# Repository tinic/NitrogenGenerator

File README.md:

# Nitrogen Generator for Home Brewing

> DIY membrane nitrogen generator for **nitro cold brew coffee**, **nitro stout**, and beverage push-gas service. Extracts **99.5%+ pure N₂** from compressed air. Total build cost **$2,222** — about half the price of commercial alternatives like NitroBev 360 or NitroBrew.

## At a glance

| Spec | Value |
|---|---|
| Output flow | 50 L/h (2 CFH) at 100 PSI |
| Output purity | 99.5%+ nitrogen (≤0.5% O₂) |
| Compressed-air input | ≤ 30 L/h (1 CFM) |
| Operating pressure | 75–100 PSI |
| Air-to-N₂ ratio | ~5:1 |
| Power | 120/240 V AC (idle = 0 W; runs only when refilling) |
| Membrane | KL-AIR MNH-1512A |
| Holding tank | 5 gal Cornelius keg |
| Total cost | **$2,222** |

### Cost vs. commercial alternatives

| Option | Cost |
|---|---|
| **This DIY build** | **$2,222** |
| NitroBev 360 | ~$4,500 |
| Industrial PSA nitrogen generator | $8,000+ |

## Motivation

As a home brewer CO₂ is the gas of choice for most purposes, including pushing beverages to the tap. But sometimes you don't want to just serve beer but also cold brew coffee and other non-carbonated beverages. In most cases a simple N₂ cylinder does the job — but given that air is 78% nitrogen, why not just extract it from the air? Recently products like NitroBev 360 have introduced this possibility on a small scale, at a price. Given the huge margins these niche products have to have, my thought was to build a nitrogen generator from scratch for less.

**Use cases this build is sized for:**

- Nitro cold brew coffee on draft
- Nitro stout / Guinness-style cascading head
- Wine and whiskey blanketing during long pours
- Generic beverage push gas where CO₂ would over-carbonate

## How nitrogen generators work

This project uses **membrane separation**. A membrane-based nitrogen generator works by passing compressed air through a semi-permeable membrane made of bundles of hollow polymer fibers. Oxygen and water vapor molecules, being smaller and having a higher permeation rate, pass through the membrane walls and are vented out as permeate. Nitrogen molecules, being larger and slower to permeate, remain inside the fibers and exit at the outlet as a high-purity nitrogen stream. Purity is adjustable down to about 0.5% residual oxygen — well within spec for beverage service.

A membrane generator needs **continuous compressed-air flow** to work. The separation relies on a sustained pressure differential across the fiber walls; if the air supply is intermittent or undersized, the differential collapses and oxygen leaks straight through. The membrane is also engineered for a specific air-flow band — undershoot it and the gas dynamics break down well before you're starving on volume.

A small **needle valve on the membrane output** controls purity. Open it too far and the residence time inside the fiber drops, producing high-O₂ output. Close it too far and most of your compressed air is dumped overboard as permeate, killing efficiency. This adjustment is per-membrane and is the single most important calibration step in the build.

The membrane needs **clean air**. Compressed air carries dust, oil aerosols, water vapor, and hydrocarbons; any of those will foul the polymer fibers. Without proper filtration, a membrane that should last *years* will die in *hours*. We filter down to **0.01 µm** before the air sees the membrane.

### Membrane vs. PSA — why membrane

PSA (Pressure Swing Adsorption) generators reach higher purity (down to a few ppm O₂) but use molecular-sieve beds, twin-tower switching valves, and large compressors — overkill for home use, expensive, and noisy. Membrane is the right scale here: no moving parts, low power, scales down to 50 L/h cleanly, and 99.5% purity is more than enough for beverage service.

## Goals & target metrics

Most commercial large-scale nitrogen equipment is built for continuous N₂ blanketing. We don't need that — a home brewer fills a keg now and then. The design priorities:

- Optimize for **low power** and **casual use**
- **Idle = zero power** (the system only runs when nitrogen is being made)
- Use **readily available, serviceable** components
- **Reasonable N₂ output** for the application — one keg per hour is plenty
- **Portable** — fits in a stainless enclosure, plugs into 120 V
- Reuse equipment home brewers already have (Cornelius keg as accumulator)

Resulting numbers:

- **120/240 V household power** — works on a generator too
- **~50 L/h (2 CFH)** N₂ output — about one keg per hour
- **≤30 L/h (1 CFM)** compressed-air input — small quiet portable compressor is fine
- **100 PSI max** system pressure — Cornelius keg territory

## Skills required

- Hands-on experience with pressurized vessels (kegging-pressure literacy is enough)
- Programming a PLC, Arduino, or microcontroller — the controller is custom firmware here, but ladder logic is fine too
- Comfort with NPT and 8 mm push-in pneumatic fittings, basic leak chasing
- Reading a P&ID
- Multimeter and soldering iron at the level of "I've put together a kit before"

## Bill of materials

These are the actual parts I bought, with what I paid. Substitutes are fine where noted; the membrane and the air filter are the two parts you should not cheap out on.

| # | Component | Model / part | Source | Paid | Notes |
|---|---|---|---|---|---|
| 1 | Nitrogen membrane | [MNH-1512A](./docs/MNH-1512A.pdf) | KL-AIR (Alibaba) | $400 | 50 L/h @ 100 PSI, 99.5%; 120 PSI max input |
| 2 | 3-stage air filter | PneumaticPlus SAFU460-N04-MEP | Amazon | $200 | 0.01 µm coalescing final stage — **don't skimp** |
| 3 | Air compressor | Makita MAC100Q | Hardware store | $250 | Quiet, ~1 CFM, oil-free |
| 4 | O₂ analyzer | FORENSICS O₂ Analyzer | Amazon | $200 | 0–30%, must support flow-through (tube fitting) |
| 5 | Holding tank | 5 gal Cornelius keg | Homebrew supplier | $130 | |
| 6 | Controller | Custom STM32G030 PCB | DigiKey + PCBWay | $130 | $80 BOM + $50 for 5 prototype boards. Click PLC works too (~$300) |
| 7 | Solenoid valves (×2) | AirTAC 2WA030-08 | Amazon | $80 | 24 V DC, normally closed, 1/4″ NPT, Viton seals |
| 8 | Needle valves (×2) | SURUIKE INDUSTRY 3 mm orifice | Amazon | $40 | Stainless, 1/4″ NPT |
| 9 | Pressure transducers (×2) | AUTEX 0–200 PSI | Amazon | $52 | 1/8″-27 NPT, with connector harness |
| 10 | Check valve | Low-cracking-pressure (<2 PSI) | Hardware store | $15 | |
| 11 | Fittings, tubing, cable | Mixed NPT + 8 mm push-in | Hardware store | ~$200 | |
| 12 | Enclosure | Stainless steel, laser-cut + bent | OshCut | $380 | 17-gauge (1.9 mm) — overkill, powder-coated steel halves the price |
| | | | **Total** | **$2,222** | |

### Don't buy these mistakes

- **Used eBay membranes.** No seller can verify the polymer fibers haven't been clogged with oil or particulates. A fouled membrane looks fine but won't separate. Spend the $400 new.
- **Oversized membranes.** I once snagged an "almost free" deal on a membrane that turned out to need **170 L/min (6 CFM)** of input air. That's an industrial compressor. Read the datasheet's input-flow column before you click buy.
- **Harbor Freight 5 µm filters.** Membrane manufacturers spec **0.01 µm** for a reason. A coarse filter will reduce your membrane lifetime from years to hours. Don't.

## System design

### Pneumatic schematic

The KiCad source for the P&ID lives at [`PnID.kicad_sch`](./PnID.kicad_sch).

### Control logic — solenoid sequence

The two solenoids (input air, output nitrogen) gate when air enters the membrane and when nitrogen leaves it. The controller runs this loop:

1. When **NitrogenPressure1** (holding-tank side) drops below **75 PSI**, open **AirSolenoid1** (input) to start filtering.
2. Hold **NitrogenSolenoid1** (output) closed until **AirPressure1** (membrane side) reaches **75 PSI**. This guarantees the membrane is at full operating pressure before any gas hits the keg, so the first nitrogen is at full purity.
3. When **NitrogenPressure1** reaches **100 PSI**, close both solenoids and return to step 1.

Short hysteresis timers (5–10 s) stagger the solenoid transitions to avoid oscillation around the setpoint.

### Safety interlocks

The controller continuously enforces:

- **AirPressure1 < 75 PSI at any point** → both solenoids closed. Prevents back-feed and nitrogen loss from the keg.
- **AirPressure1 > 120 PSI at any point** → both solenoids closed. The membrane's mechanical limit; exceed it and the fibers can shatter.
- **Either pressure < 0 or > 150 PSI** (out of physical range) → both solenoids closed. Fail-safe for sensor failure.

### What the firmware does on every tick

The state machine in [`CubeMX/mcp.cpp`](./CubeMX/mcp.cpp) (function `Slice()`) reduces to:

```
read AirPressure1, NitrogenPressure1
if any sensor out of range:           goto FAULT
if AirPressure1 > 120:                goto FAULT
if AirPressure1 < 75:                 close both solenoids, hold
if NitrogenPressure1 >= 100:          close both solenoids
if NitrogenPressure1 < 75:            open AirSolenoid1 (after 10 s soft-start delay)
if AirPressure1 >= 75:                open NitrogenSolenoid1
update LCD with pressures + state
```

The status LCD is a 192×64 monochrome panel driven via SPI (ST7525) using the [constixel](https://github.com/tinic/constixel) graphics library. UI rendering lives in [`CubeMX/screen.cpp`](./CubeMX/screen.cpp).

## Calibration

Two needle valves to set, in this order: input first (membrane protection), then output (purity).

### Input needle valve — protect the membrane

The input needle valve dampens the pressure step that hits the membrane when the input solenoid suddenly opens. Without it, the membrane sees the full upstream pressure as a step function and the polymer fibers can shatter. **Set this before assembling the rest of the system.**

1. Rig the input needle valve to a regulated air supply.
2. Step the upstream pressure to 100 PSI suddenly.
3. The downstream side should feel like 5–10 PSI bleeding out of a compressor — not a "bang".
4. If you hear a bang, tighten the needle until the step is gentle.

### Output needle valve — set the purity

This sets your final O₂ content. **You need an O₂ analyzer for this step**; eyeballing it is not possible.

1. Set the output needle valve to fully closed during initial leak-testing of the rest of the system.
2. To avoid blasting the analyzer with raw permeate-rich air, open the output valve **only ~4 turns** before any nitrogen flow.
3. Connect the O₂ analyzer directly to the system output via tubing — **no air gaps in the path**, room air contaminating the sample is the #1 calibration mistake.
4. Start the system and slowly close the output needle valve while watching the analyzer. O₂ will start dropping once the membrane has time to flush.
5. Continue patiently — gas takes minutes to flush the analyzer chamber. Make 1/8-turn adjustments and wait 2–5 minutes between them.
6. Stop when you reach **≤ 1% O₂**. Closing further shoots permeate-to-product ratio above ~5:1 with no purity gain.
7. **What success feels like:** at 99.5% purity and 50 L/h, you can barely feel air on your lips at the output. That's normal. If you can clearly feel flow, you're at higher O₂.

Mark the final valve position with a paint pen so you can return to it after maintenance.

## Repository layout

```
.
├── CubeMX/                   STM32G030 firmware (CMake + arm-none-eabi-gcc)
│   ├── mcp.cpp               Control state machine (Slice())
│   ├── screen.cpp            LCD UI rendering (constixel-based)
│   ├── build.sh              One-shot build
│   └── CMakeLists.txt
├── NitrogenGenerator.kicad_*  KiCad PCB project (controller board)
├── PnID.kicad_sch            P&ID schematic of the pneumatic system
├── solidworks/               Mechanical CAD for the stainless enclosure
├── docs/                     Datasheets (membrane, components)
├── images/                   Photos and renders used in this README
├── kicad-makefile/           Production-file generation (gerbers, BOM)
└── pnid-lib/                 KiCad symbols for P&ID drawing
```

## Building

### Firmware

```bash
git clone https://github.com/tinic/nitrogengenerator.git
cd nitrogengenerator/CubeMX
./build.sh
```

Requirements:

- [ARM GCC toolchain](https://developer.arm.com/Tools%20and%20Software/GNU%20Toolchain) (`arm-none-eabi-gcc`)
- CMake 3.22+
- Python 3 (for font and image asset conversion)

Flash with your favourite STM32 programmer (ST-Link, Black Magic Probe, etc.) — the build emits a `.elf`, `.bin`, and `.hex` in `CubeMX/build/`.

### PCB

Open `NitrogenGenerator.kicad_pro` in KiCad 7+. Production files (gerbers, drill, BOM) are generated by:

```bash
make -C kicad-makefile
```

Send the resulting zip to PCBWay or any fab. 5 prototype boards came out to ~$50 including shipping at the time of writing.

### Enclosure

`solidworks/` contains the mechanical CAD. The DXF flat patterns in that folder are what I sent to OshCut. Powder-coated steel will halve the cost vs. the 17-gauge stainless I used.

## Reproduction checklist

If you want to build this exact one:

1. Order MNH-1512A from KL-AIR on Alibaba (~$400 + shipping/tariffs).
2. Order PneumaticPlus SAFU460-N04-MEP 3-stage filter (~$200).
3. Get a Makita MAC100Q (or any quiet 1 CFM oil-free compressor).
4. Order 2× AirTAC 2WA030-08 solenoids and 2× SURUIKE 3 mm needle valves (~$120 total).
5. Order the controller PCB from PCBWay using the KiCad files in this repo.
6. Source DigiKey BOM for the PCB (~$80).
7. Order the enclosure from OshCut using `solidworks/` DXFs (or build your own from any rigid material).
8. Flash the firmware: `cd CubeMX && ./build.sh`.
9. Wire per [`PnID.kicad_sch`](./PnID.kicad_sch).
10. Calibrate per the procedure above. Push your first nitro cold brew.

## Safety

- **High-pressure system.** Wear safety glasses while pressurizing. Pressure-test all joints with soap solution before energising electrically.
- **Membrane shock.** Never exceed 120 PSI on the membrane input — the soft-start needle valve is what protects you. Don't ever bypass it.
- **Asphyxiation hazard.** N₂ at 99.5% will displace breathable oxygen in a small enclosed space. Keep the area ventilated. The output stream is small (50 L/h), but a leak in a closet matters.
- **Electrical.** 24 V DC is present at the solenoid driver outputs. Use an IP-rated enclosure if the unit lives anywhere humid (kegerators, garages).
- **Pressure relief.** Install a relief valve set to 110 PSI between the membrane output and the keg, in case the output solenoid fails closed and the input doesn't shut off.

## Troubleshooting

| Problem | Symptoms | Likely cause | Fix |
|---|---|---|---|
| No N₂ flow | Tank pressure stays flat | Output valve too closed; membrane fouled; control fault | Open output 1/4 turn; check filter element; check sensor readings on LCD |
| O₂ reading > 2% | Analyzer never drops below 2% | Output valve too open; membrane degraded; air gap in sample line | Close output 1/8 turn; verify no leaks in analyzer hose; if problem persists with new tubing, suspect membrane end-of-life |
| Flow rate < 40 L/h | Slow keg fill | Filter element clogged; output valve too closed; input pressure low | Replace filter element; open output slightly; check compressor duty |
| Compressor short-cycles | Compressor kicks on every few seconds | Check valve cracking pressure too high or leaking | Replace check valve with one that opens below 2 PSI |
| Initial high O₂ on startup | Analyzer reads room air for the first few minutes | Normal — gas needs to flush analyzer chamber | Wait 2–5 minutes after first start before adjusting |
| LCD blank but solenoids click | Display SPI fault | Loose ribbon cable; constixel bug | Reseat the LCD connector; reflash firmware |

## Maintenance

| Interval | Task |
|---|---|
| Weekly (in active use) | Drain water from filter bowls; verify O₂ reading on a test pull |
| Monthly | Visual leak check; tighten compression fittings if any have shifted |
| Quarterly | Replace 0.01 µm coalescing filter element; inspect tubing for kinks |
| Annually | Calibrate pressure transducers against a known gauge; full system pressure test |

## FAQ

<details>
<summary><b>Can I just use a CO₂ cylinder instead?</b></summary>

CO₂ is the wrong gas for nitro. The cascading creamy mouthfeel comes from N₂'s low solubility in water — CO₂ over-carbonates and changes the taste. For stout faucets and nitro cold brew you need nitrogen (or a 75/25 N₂/CO₂ blend for some stouts).
</details>

<details>
<summary><b>How long does the membrane last?</b></summary>

**Years** with proper 0.01 µm pre-filtration and clean dry air. **Hours** if the filter element fails or you let oil aerosols through. The filter is the single biggest determinant of membrane lifetime.
</details>

<details>
<summary><b>What's the difference between nitro coffee gas and stout gas?</b></summary>

Nitro cold brew uses ~100% N₂. Traditional Guinness-style stout faucets use a 75/25 N₂/CO₂ blend ("Beer Gas") because the small CO₂ fraction keeps a bit of carbonation in the beer. This generator produces 99.5%+ N₂; for stout-blend service you'd add a CO₂ cylinder and a blender.
</details>

<details>
<summary><b>Do I need a stout faucet?</b></summary>

Yes — a stout faucet has a restrictor plate that breaks dissolved nitrogen out of solution as the beverage passes, which is what creates the cascading head. A standard tap won't produce the effect.
</details>

<details>
<summary><b>Is this safe to run in a small room?</b></summary>

The output flow (50 L/h) is small enough that a normally ventilated room is fine. **Don't** run it in a sealed closet, walk-in cooler, or fermentation chamber without a vent — N₂ is an asphyxiant at high concentrations and you won't notice it before you're hypoxic.
</details>

<details>
<summary><b>Why a custom PCB instead of a Click PLC or Arduino?</b></summary>

The PLC works fine — my first prototype used one — but it's bulky, uses ladder logic, and the BOM is ~$300. The custom STM32G030 board is $130 in parts and parts-on-board, fits in the same enclosure as the pneumatics, and drives the LCD directly. An Arduino would also work at similar BOM cost.
</details>

<details>
<summary><b>Can I scale this up?</b></summary>

Yes — the MNH-2024A membrane outputs ~120 L/h with a proportionally larger compressor (~170 L/h input). Same control logic, bigger plumbing, bigger compressor (which kills the "quiet portable" goal — at that scale you're better off with PSA).
</details>

## Related

- KL-AIR membranes: [alibaba.com](https://www.alibaba.com/) — search "MNH-1512A"
- PneumaticPlus filters: [PneumaticPlus.com](https://pneumaticplus.com/)
- OshCut laser cutting: [oshcut.com](https://www.oshcut.com/)
- PCBWay: [pcbway.com](https://www.pcbway.com/)
- constixel graphics library: [github.com/tinic/constixel](https://github.com/tinic/constixel)

## License

This project is released under [The Unlicense](./LICENSE) — public-domain dedication. Use any part of it for any purpose, commercial or private. **No warranty, no liability.** If you blow yourself up with a misconfigured nitrogen system, that is on you, not me.

---

<sub>If you build one, tag your photos with **#DIYNitrogenGenerator** so others can find it. Pull requests with improvements, alternative BOMs, or photos of working builds welcome.</sub>

<!-- keywords: DIY nitrogen generator, home brewing nitrogen, membrane nitrogen separator, nitro cold brew at home, nitro coffee maker DIY, nitrogen for cold brew, nitro stout home, nitrogen generator from air, MNH-1512A, KL-AIR nitrogen membrane, PneumaticPlus SAFU460, NitroBev 360 alternative, NitroBrew DIY, PSA vs membrane nitrogen, nitrogen on draft, beverage push gas, Cornelius keg nitrogen, stout faucet nitrogen, STM32G030 controller, oxygen analyzer calibration, hollow fiber membrane, nitrogen purity 99.5%, compressed air filter 0.01 micron, oil-free compressor nitrogen, soft start needle valve, asphyxiation safety, beer gas blend, KiCad PCB project, open hardware nitrogen, brewing automation -->

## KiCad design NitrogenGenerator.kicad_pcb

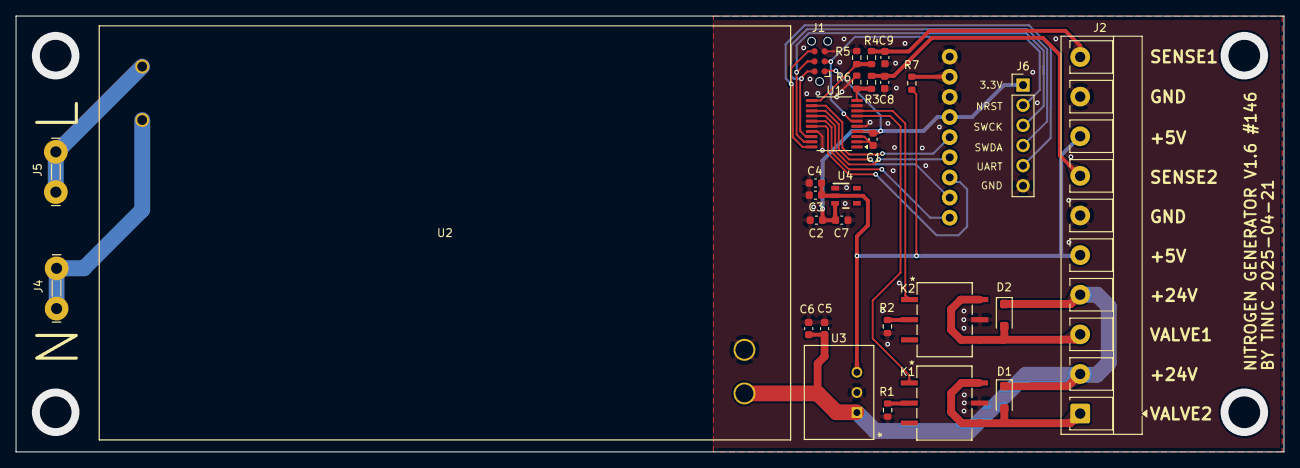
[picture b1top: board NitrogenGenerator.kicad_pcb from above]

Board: 2 copper layers, 160.0 x 55.0 mm, 30 parts (1 on the bottom side), 26 nets.

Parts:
C1, C2, C3: 0.1uF; C_0603_1608Metric
C4, C5, C6, C7: 4.7uF; C_0603_1608Metric
C8, C9: 22nF; C_0603_1608Metric
D1, D2: 1N4007; D_SOD-123F
J1: Conn_ARM_SWD_TagConnect_TC2030-NL; Tag-Connect_TC2030-IDC-NL_2x03_P1.27mm_Vertical
J2: Screw_Terminal_01x10; TerminalBlock_RND_205-00284_1x10_P5.00mm_Vertical
J3: ERM19264-4; ERM19264DNS-4
J4, J5: 726386-2; CONN_726386-2_TEC
J6: Conn_01x06_Pin; PinHeader_1x06_P2.54mm_Vertical
K1, K2: AA28F-R1; SMD6_AA28F-R1_BTI
R1, R2: 1.6K; R_0603_1608Metric
R3, R4: 10K; R_0603_1608Metric
R5, R6: 20K; R_0603_1608Metric
R7: 100; R_0603_1608Metric
U1: STM32G030F6Px; TSSOP-20_4.4x6.5mm_P0.65mm
U2: IRM-45-24; IRM-45_MWU
U3: R-78E5.0-0.5; R-78E-0.5_RCP
U4: TLV70433DBVR

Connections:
+3.3V: C1.1, C2.1, C7.1, J1.1 (VCC), J3.4, J6.1, U1.4 (VDD), U4.3 (OUT)
+5V: C3.1, C4.1, J2.5, J2.8, R7.2, U3.3 (+VOUT), U4.2 (IN)
+24V: C5.1, C6.1, D1.1 (K), D2.1 (K), J2.2, J2.4, U2.3 (V+), U3.1 (+VIN)
/CTRL_VALVE_IN: K1.1, U1.7 (PA0)
/CTRL_VALVE_OUT: K2.1, U1.8 (PA1)
/LCD_CD: J3.8, U1.13 (PA6)
/LCD_CS: J3.9, U1.15 (PA8/PB0/PB1/PB2)
/LCD_RESET: J3.7, U1.16 (PA9/PA11)
/LCD_SCK: J3.5, U1.12 (PA5)
/LCD_SDA: J3.6, U1.14 (PA7)
/LOAD_VALVE_IN: D1.2 (A), J2.1, K1.4, K1.6
/LOAD_VALVE_OUT: D2.2 (A), J2.3, K2.4, K2.6
/PRESSURE_INPUT: R3.1, R6.2, U1.10 (PA3)
/PRESSURE_OUTPUT: R4.1, R5.2, U1.11 (PA4)
/SWCLK: J1.4 (SWCLK), J6.3, U1.19 (PA14/PA15)
/SWDIO: J1.2 (SWDIO), J6.4, U1.18 (PA13)
/UART1_TX: J1.6 (SWO), J6.5, U1.20 (PB3/PB4/PB5/PB6)
/~RESET: J1.3 (~RESET), J6.2, U1.6 (NRST)
GND: C1.2, C2.2, C3.2, C4.2, C5.2, C6.2, C7.2, C8.1, C9.1, J1.5 (GND), J2.6, J2.9, J3.1, J3.3, J6.6, K1.5, K2.5, R1.1, R2.1, R5.1, R6.1, U1.2 (PB9/PC14), U1.3 (PC15), U1.5 (VSS), U1.9 (PA2), U1.17 (PA10/PA12), U2.4 (V-), U3.2 (GND), U4.1 (GND)
unnamed: C8.2, J2.7, R3.2
unnamed: C9.2, J2.10, R4.2
unnamed: J3.2, R7.1
unnamed: K1.2, R1.2
unnamed: K2.2, R2.2
unnamed: J5.1, J5.2, U2.1 (AC/L)
unnamed: J4.1, J4.2, U2.2 (AC/N)

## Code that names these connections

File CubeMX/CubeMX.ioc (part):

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Mcu.Name=STM32G030F6Px
Mcu.Package=TSSOP20
Mcu.UserName=STM32G030F6Px
PA0.GPIOParameters=GPIO_Label
PA0.GPIO_Label=SOLENOID_VALVE1
PA0.Signal=GPIO_Output
PA1.GPIOParameters=GPIO_Label
PA1.GPIO_Label=SOLENOID_VAVLE2
PA1.Signal=GPIO_Output
PA13.Mode=Serial_Wire
PA13.Signal=SYS_SWDIO
PA14-BOOT0.Mode=Serial_Wire
PA14-BOOT0.Signal=SYS_SWCLK
PA14-BOOT0__PA15.StandardMode=true
PA3.GPIOParameters=GPIO_Label
PA3.GPIO_Label=ANALOG_SENSOR1
PA3.Mode=IN3
PA3.Signal=ADC1_IN3
PA4.GPIOParameters=GPIO_Label
PA4.GPIO_Label=ANALOG_SENSOR2
PA4.Mode=IN4
PA4.Signal=ADC1_IN4
PA5.GPIOParameters=GPIO_Label
PA5.GPIO_Label=LCD_SCK
PA5.Mode=TX_Only_Simplex_Unidirect_Master
PA5.Signal=SPI1_SCK
PA6.GPIOParameters=GPIO_Label
PA6.GPIO_Label=LCD_CD
PA6.Signal=GPIO_Output
PA7.GPIOParameters=GPIO_Label
PA7.GPIO_Label=LCD_SDA
PA7.Mode=TX_Only_Simplex_Unidirect_Master
PA7.Signal=SPI1_MOSI
PB0__PB1__PB2__PA8.StandardMode=true
PB3__PB4__PB5__PB6.StandardMode=true
PB6.Mode=Asynchronous
PB6.Signal=USART1_TX
PB7.Mode=Asynchronous
PB7.Signal=USART1_RX
PB7__PB8.StandardMode=true
PC14-OSC32_IN\ (PC14)__PB9.StandardMode=true
RCC.HSE_VALUE=8000000
RCC.SYSCLKFreq_VALUE=64000000
RCC.SYSCLKSource=RCC_SYSCLKSOURCE_PLLCLK
board=custom

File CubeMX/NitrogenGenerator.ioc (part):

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Mcu.Name=STM32G030F6Px
Mcu.Package=TSSOP20
Mcu.UserName=STM32G030F6Px
PA0.GPIOParameters=GPIO_Label
PA0.GPIO_Label=SOLENOID_VALVE1
PA0.Signal=GPIO_Output
PA1.GPIOParameters=GPIO_Label
PA1.GPIO_Label=SOLENOID_VAVLE2
PA1.Signal=GPIO_Output
PA11\ [PA9].GPIOParameters=GPIO_Label
PA11\ [PA9].GPIO_Label=LCD_RESET
PA11\ [PA9].Signal=GPIO_Output
PA13.Mode=Serial_Wire
PA13.Signal=SYS_SWDIO
PA14-BOOT0.Mode=Serial_Wire
PA14-BOOT0.Signal=SYS_SWCLK
PA14-BOOT0__PA15.StandardMode=true
PA3.GPIOParameters=GPIO_Label
PA3.GPIO_Label=ANALOG_SENSOR1
PA3.Mode=IN3
PA3.Signal=ADC1_IN3
PA4.GPIOParameters=GPIO_Label
PA4.GPIO_Label=ANALOG_SENSOR2
PA4.Mode=IN4
PA4.Signal=ADC1_IN4
PA5.GPIOParameters=GPIO_Label
PA5.GPIO_Label=LCD_SCK
PA5.Mode=TX_Only_Simplex_Unidirect_Master
PA5.Signal=SPI1_SCK
PA6.GPIOParameters=GPIO_Label
PA6.GPIO_Label=LCD_CD
PA6.Signal=GPIO_Output
PA7.GPIOParameters=GPIO_Label
PA7.GPIO_Label=LCD_SDA
PA7.Mode=TX_Only_Simplex_Unidirect_Master
PA7.Signal=SPI1_MOSI
PB0.Signal=GPIO_Output
PB0__PB1__PB2__PA8.StandardMode=false
PB3__PB4__PB5__PB6.StandardMode=true
PB7__PB8.StandardMode=true
PC14-OSC32_IN\ (PC14)__PB9.StandardMode=true
RCC.HSE_VALUE=8000000
RCC.SYSCLKFreq_VALUE=64000000
RCC.SYSCLKSource=RCC_SYSCLKSOURCE_PLLCLK
board=custom

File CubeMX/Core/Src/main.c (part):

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  __HAL_RCC_GPIOA_CLK_ENABLE();

  /*Configure GPIO pin Output Level */
  HAL_GPIO_WritePin(GPIOA, SOLENOID_VALVE1_Pin|SOLENOID_VAVLE2_Pin|LCD_CD_Pin|LCD_RESET_Pin, GPIO_PIN_RESET);

  /*Configure GPIO pin Output Level */
  HAL_GPIO_WritePin(GPIOB, GPIO_PIN_0, GPIO_PIN_RESET);

  /*Configure GPIO pins : PB7 PB8 PB9 PB1
                           PB2 PB3 PB4 PB5
                           PB6 */
  GPIO_InitStruct.Pin = GPIO_PIN_7|GPIO_PIN_8|GPIO_PIN_9|GPIO_PIN_1
                          |GPIO_PIN_2|GPIO_PIN_3|GPIO_PIN_4|GPIO_PIN_5
                          |GPIO_PIN_6;
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  GPIO_InitStruct.Pull = GPIO_NOPULL;
  HAL_GPIO_Init(GPIOB, &GPIO_InitStruct);

  /*Configure GPIO pins : PC14 PC15 */
  GPIO_InitStruct.Pin = GPIO_PIN_14|GPIO_PIN_15;
  GPIO_InitStruct.Mode = GPIO_MODE_ANALOG;
  GPIO_InitStruct.Pull = GPIO_NOPULL;
  HAL_GPIO_Init(GPIOC, &GPIO_InitStruct);

  /*Configure GPIO pins : SOLENOID_VALVE1_Pin SOLENOID_VAVLE2_Pin LCD_CD_Pin LCD_RESET_Pin */
  GPIO_InitStruct.Pin = SOLENOID_VALVE1_Pin|SOLENOID_VAVLE2_Pin|LCD_CD_Pin|LCD_RESET_Pin;
  GPIO_InitStruct.Mode = GPIO_MODE_OUTPUT_PP;
  GPIO_InitStruct.Pull = GPIO_NOPULL;
  GPIO_InitStruct.Speed = GPIO_SPEED_FREQ_LOW;
  HAL_GPIO_Init(GPIOA, &GPIO_InitStruct);

  /*Configure GPIO pins : PA2 PA8 PA12 PA15 */
  GPIO_InitStruct.Pin = GPIO_PIN_2|GPIO_PIN_8|GPIO_PIN_12|GPIO_PIN_15;
  GPIO_InitStruct.Mode = GPIO_MODE_ANALOG;
  GPIO_InitStruct.Pull = GPIO_NOPULL;
  HAL_GPIO_Init(GPIOA, &GPIO_InitStruct);

  /*Configure GPIO pin : PB0 */
  GPIO_InitStruct.Pin = GPIO_PIN_0;
  GPIO_InitStruct.Mode = GPIO_MODE_OUTPUT_PP;
  GPIO_InitStruct.Pull = GPIO_NOPULL;
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
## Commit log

2025-05-27 Edit README.md
2026-05-02 README rewrite + Unlicense
    - Restore the original first-person voice + technical reasoning
    (motivation, membrane physics, "don't buy these mistakes" warnings).
    - Concrete BOM with actual receipts ($2,222 total) instead of marketing
    cost ranges; per-component links and photos.
    - New sections: cost vs. NitroBev 360 / PSA, scaling-up FAQ, firmware
    pseudocode (Slice() state machine), repo layout, reproduction
2026-05-02 README: badges row (license, last-commit, KiCad, STM32, SolidWorks, Unlicense)
    Carry-forward of the badges added in bf90bea on github/main — that
    commit was on top of the old README, so these need to land fresh on
    top of the rewrite.

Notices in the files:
CubeMX/Core/Src/main.c:
Copyright (c) 2025 STMicroelectronics.
All rights reserved.
This software is licensed under terms that can be found in the LICENSE file
README.md:
License: Unlicense
